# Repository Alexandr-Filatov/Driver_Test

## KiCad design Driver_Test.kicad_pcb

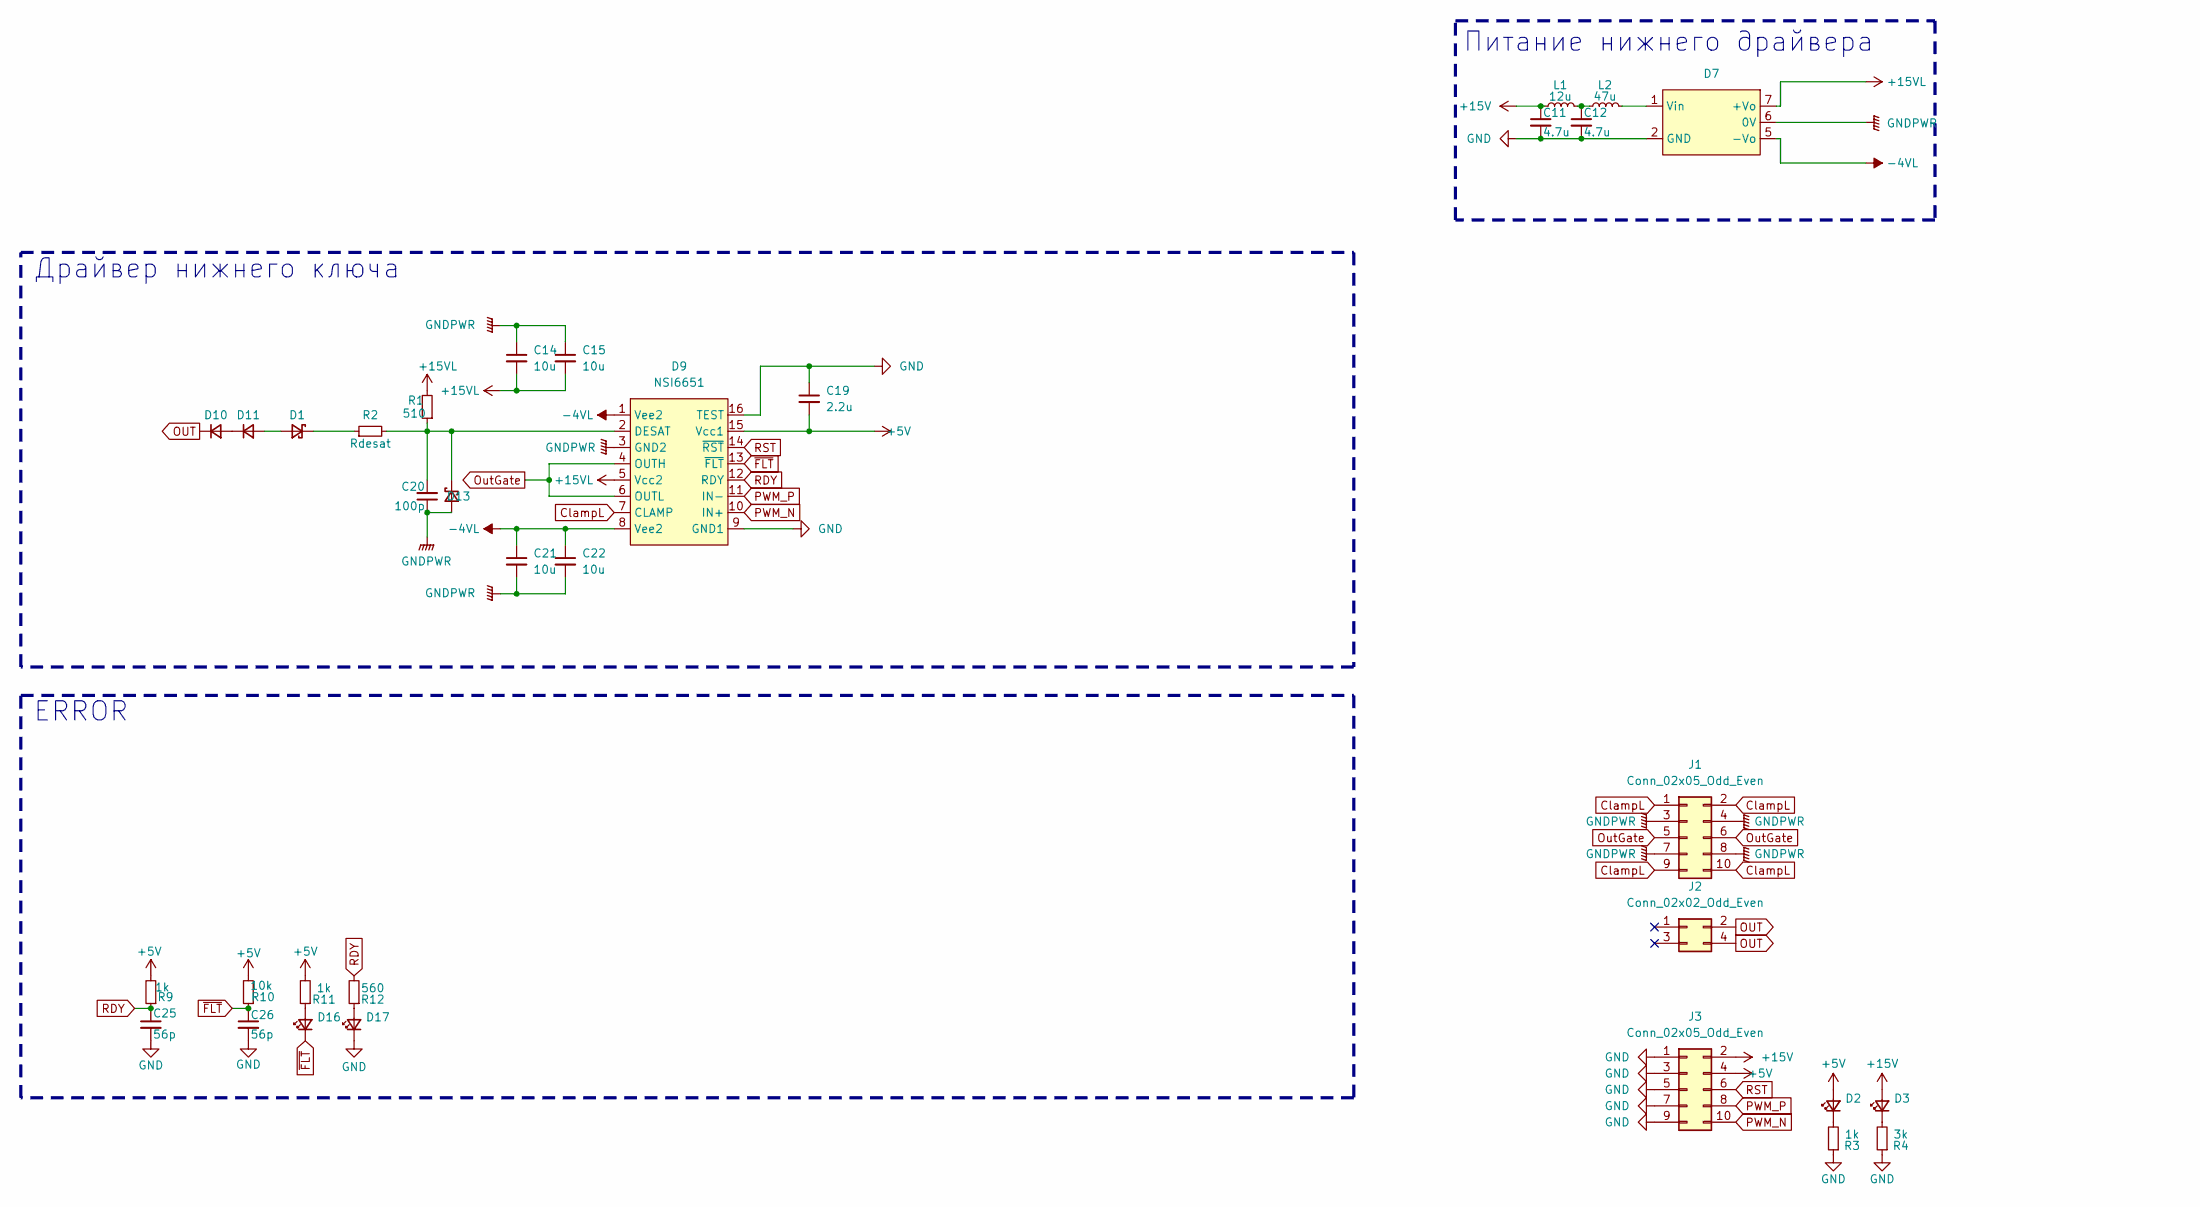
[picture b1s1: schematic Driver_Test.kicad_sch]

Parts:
C11, C12: 4.7u; C_1206_3216Metric_Pad1.33x1.80mm_HandSolder
C14, C15, C21, C22: 10u; C_1206_3216Metric_Pad1.33x1.80mm_HandSolder
C19: 2.2u; C_0805_2012Metric_Pad1.18x1.45mm_HandSolder
C20: 100p; C_0805_2012Metric_Pad1.18x1.45mm_HandSolder
C25, C26: 56p; C_0805_2012Metric_Pad1.18x1.45mm_HandSolder
D1: D_SOD-323_HandSoldering
D2, D3, D16, D17: LED_0805_2012Metric_Pad1.15x1.40mm_HandSolder
D7: QAxCx
D9: NSI6651; SOIC-16W_7.5x10.3mm_P1.27mm
D10, D11: D_Small; D_SMA_Handsoldering
D13: D_SOD-123
J1: Conn_02x05_Odd_Even; PinHeader_2x05_P2.54mm_Horizontal
J2: Conn_02x02_Odd_Even; PinHeader_2x02_P2.54mm_Horizontal
J3: Conn_02x05_Odd_Even; PinSocket_2x05_P2.54mm_Vertical
L1: 12u; L_1210_3225Metric_Pad1.42x2.65mm_HandSolder
L2: 47u; L_1812_4532Metric_Pad1.30x3.40mm_HandSolder
R1: 510; R_0805_2012Metric_Pad1.20x1.40mm_HandSolder
R2: Rdesat; R_0805_2012Metric_Pad1.20x1.40mm_HandSolder
R3, R9, R11: 1k; R_0805_2012Metric_Pad1.20x1.40mm_HandSolder
R4: 3k; R_0805_2012Metric_Pad1.20x1.40mm_HandSolder
R10: 10k; R_0805_2012Metric_Pad1.20x1.40mm_HandSolder
R12: 560; R_0805_2012Metric_Pad1.20x1.40mm_HandSolder

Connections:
+5V: C19.2, D2.2 (A), D9.15 (Vcc1), J3.4, R9.2, R10.2, R11.2
+15V: C11.1, D3.2 (A), J3.2, L1.1
+15VL: C14.2, C15.2, D7.7 (+Vo), D9.5 (Vcc2), R1.2
-15VL: C21.1, C22.1, D7.5 (-Vo), D9.1 (Vee2), D9.8 (Vee2)
ClampL: D9.7 (CLAMP), J1.1, J1.2, J1.9, J1.10
GND: C11.2, C12.2, C19.1, C25.2, C26.2, D7.2 (GND), D9.9 (GND1), D9.16 (TEST), D17.1 (K), J3.1, J3.3, J3.5, J3.7, J3.9, R3.1, R4.1
GNDPWR: C14.1, C15.1, C20.1, C21.2, C22.2, D7.6 (0V), D9.3 (GND2), D13.2 (A), J1.3, J1.4, J1.7, J1.8
unnamed: C12.1, L1.2, L2.1
unnamed: D1.2 (A), D11.2 (A)
unnamed: D1.1 (K), R2.1
unnamed: D2.1 (K), R3.2
unnamed: D3.1 (K), R4.2
unnamed: D7.1 (Vin), L2.2
unnamed: D10.2 (A), D11.1 (K)
unnamed: C20.2, D9.2 (DESAT), D13.1 (K), R1.1, R2.2
unnamed: D16.2 (A), R11.1
unnamed: D17.2 (A), R12.1
OUT: D10.1 (K), J2.2, J2.4
OutGate: D9.4 (OUTH), D9.6 (OUTL), J1.5, J1.6
PWM_N: D9.10 (IN+), J3.10
PWM_P: D9.11 (IN-), J3.8
RDY: C25.1, D9.12 (RDY), R9.1, R12.2
RST: D9.14 (~RST), J3.6
~FLT: C26.1, D9.13 (~FLT), D16.1 (K), R10.1

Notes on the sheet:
Драйвер нижнего ключа
Питание нижнего драйвера
ERROR

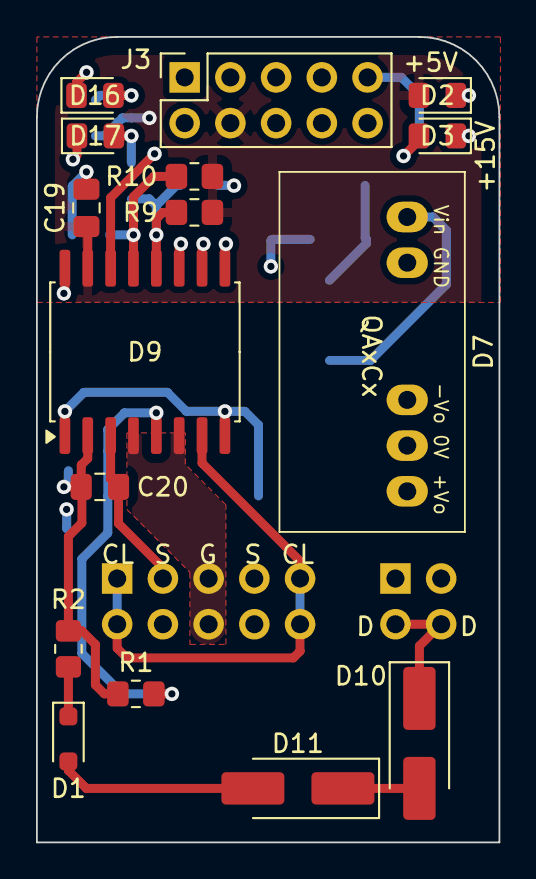
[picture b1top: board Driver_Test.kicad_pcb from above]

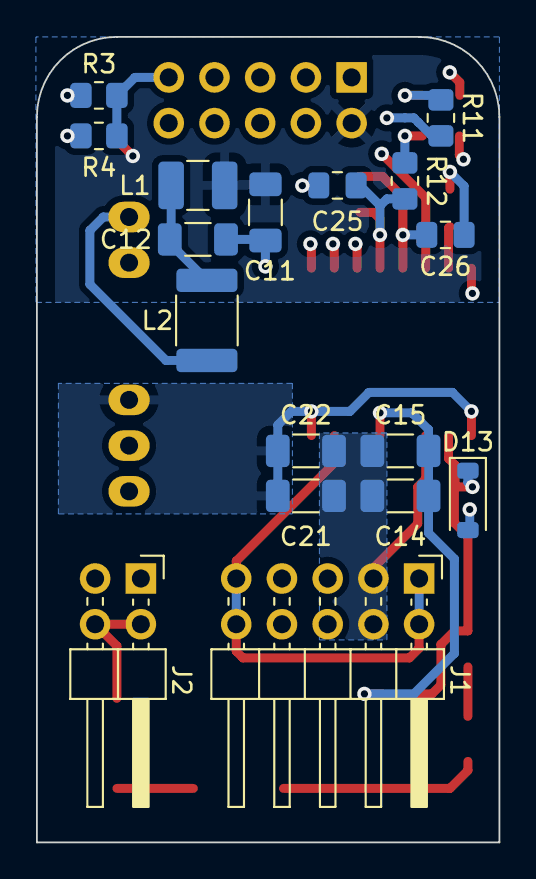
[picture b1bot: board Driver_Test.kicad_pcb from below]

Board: 4 copper layers, 25.7 x 44.8 mm, 33 parts (17 on the bottom side), 24 nets.

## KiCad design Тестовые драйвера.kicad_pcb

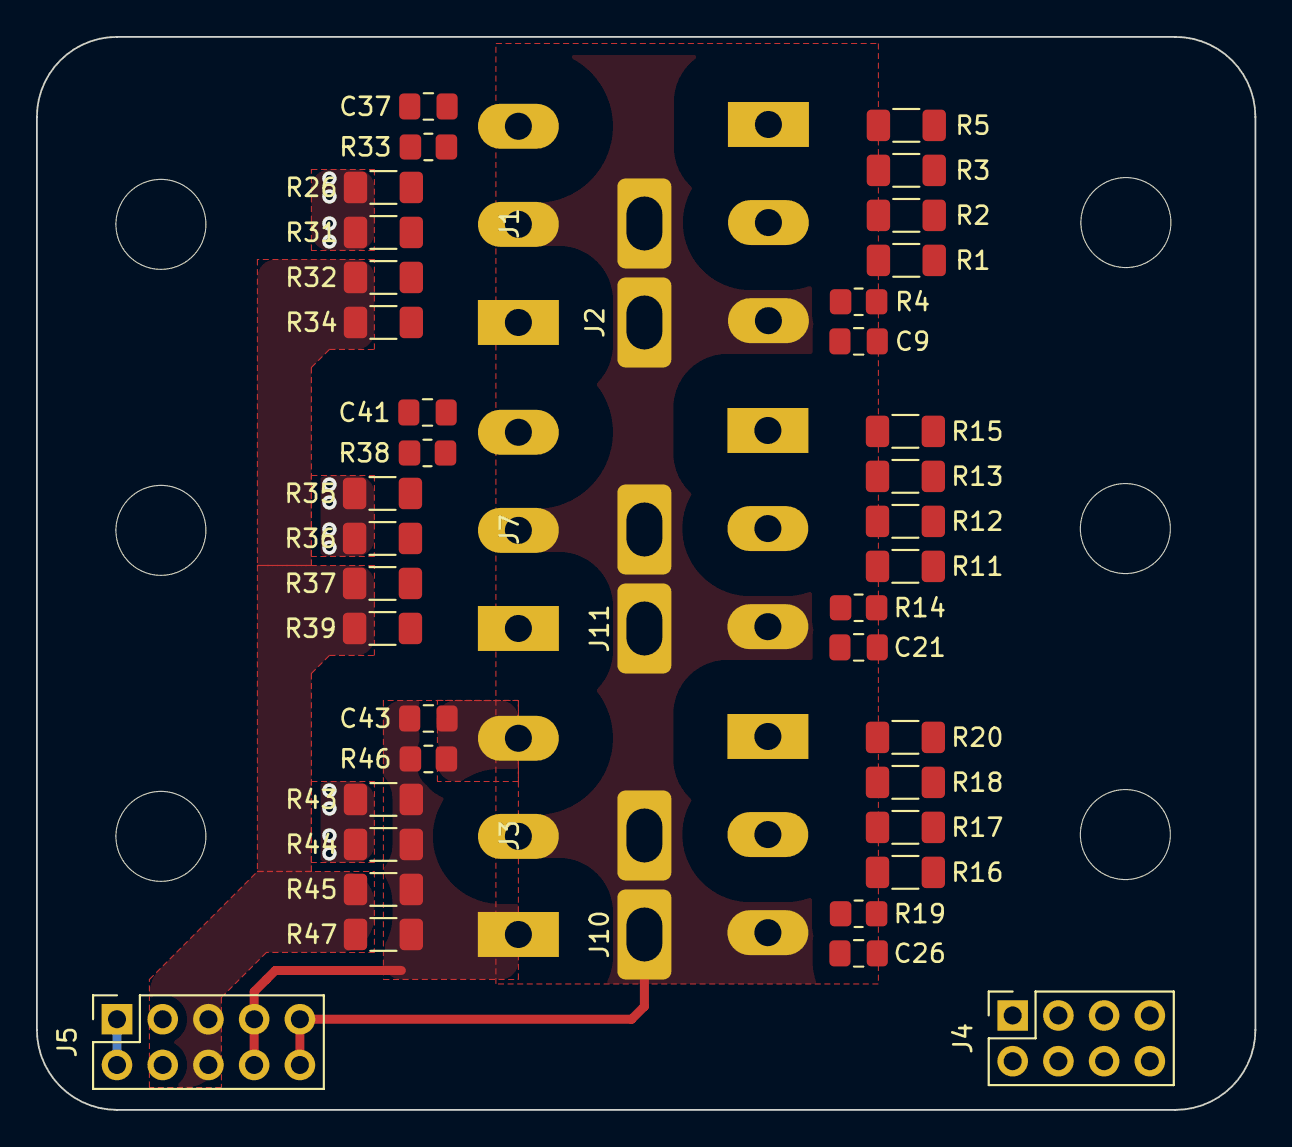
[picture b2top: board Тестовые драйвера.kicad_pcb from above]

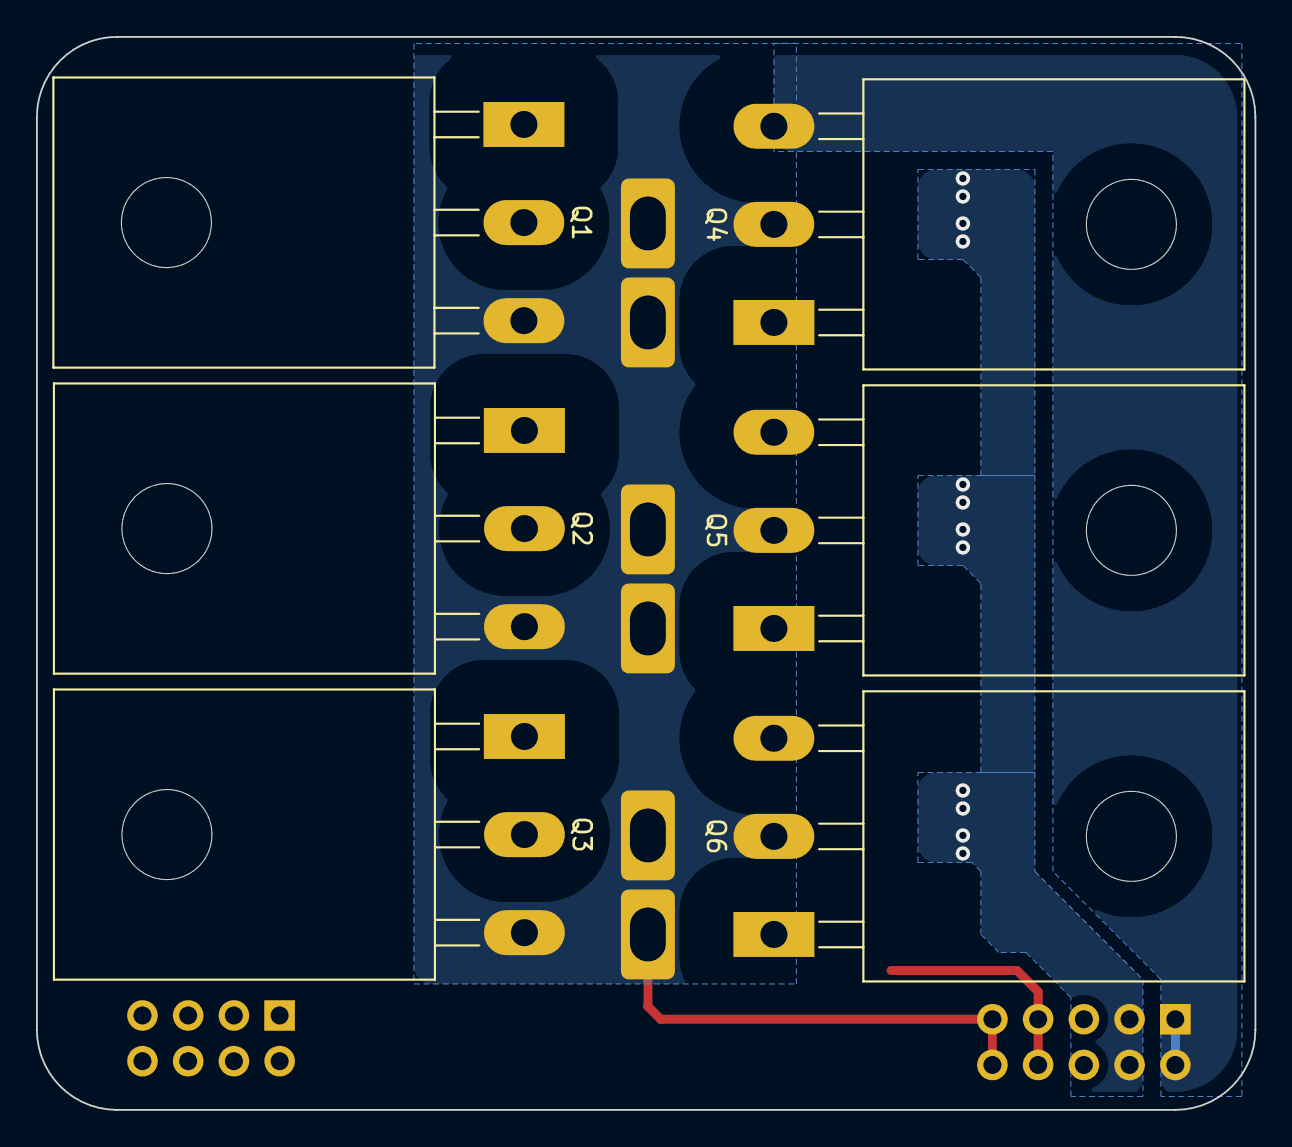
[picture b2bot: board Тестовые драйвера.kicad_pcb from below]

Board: 2 copper layers, 67.7 x 59.6 mm, 50 parts (6 on the bottom side), 9 nets.

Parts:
C9, C21, C26, C37, C41, C43: 10n; C_0805_2012Metric_Pad1.18x1.45mm_HandSolder
J1, J2, J3, J7, J10, J11: Conn_01x01; Bush_5x3
J4: Conn_01x04; PinSocket_2x04_P2.54mm_Vertical
J5: Conn_02x05_Odd_Even; PinSocket_2x05_P2.54mm_Vertical
Q1, Q2, Q3, Q4, Q5, Q6: C2M0280120D; TO-247-3_Horizontal_TabUp
R1, R2, R3, R5, R11, R12, R13, R15, R16, R17, R18, R20, R26, R31, R32, R34, R35, R36, R37, R39, R43, R44, R45, R47: 15; R_1206_3216Metric_Pad1.30x1.75mm_HandSolder
R4, R14, R19, R33, R38, R46: 10k; R_0805_2012Metric_Pad1.20x1.40mm_HandSolder

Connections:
ClampH: C9.1, C21.1, C26.1, Q1.1 (G), Q2.1 (G), Q3.1 (G), R1.2, R2.2, R3.1, R4.2, R5.1, R11.2, R12.2, R13.1, R14.2, R15.1, R16.2, R17.2, R18.1, R19.2, R20.1
ClampL: C37.1, C41.1, C43.1, J5.7, J5.8, Q4.1 (G), Q5.1 (G), Q6.1 (G), R26.2, R31.2, R32.1, R33.2, R34.1, R35.2, R36.2, R37.1, R38.2, R39.1, R43.2, R44.2, R45.1, R46.2, R47.1
GNDPWR: C37.2, C41.2, C43.2, J5.1, J5.2, Q4.3 (S), Q5.3 (S), Q6.3 (S), R33.1, R38.1, R46.1
OUT: C9.2, C21.2, C26.2, J1.1, J2.1, J3.1, J5.9, J5.10, J7.1, J10.1, J11.1, Q1.3 (S), Q2.3 (S), Q3.3 (S), Q4.2 (D), Q5.2 (D), Q6.2 (D), R4.1, R14.1, R19.1
OutH1: R1.1, R2.1, R11.1, R12.1, R16.1, R17.1
OutH2: J5.3, J5.4, R26.1, R31.1, R35.1, R36.1, R43.1, R44.1
OutL1: R3.2, R5.2, R13.2, R15.2, R18.2, R20.2
OutL2: J5.5, J5.6, R32.2, R34.2, R37.2, R39.2, R45.2, R47.2
VDC: Q1.2 (D), Q2.2 (D), Q3.2 (D)

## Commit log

2024-05-22 Нулевой коммит
2024-05-23 Полная схема
2024-05-23 Начал разводку платы
2024-06-08 Расположил на плате
2024-06-09 Разве драйвера
2024-06-19 Закончил схему и разводку платы
2025-08-28 Пытаюсь сделать как у вольфспида
2025-09-10 VER1.0: пробую уложиться в ширину транзисторов
2025-10-13 Пытаюсь уложиться в контур транзисторов
2025-10-14 Определились с ТЗ
2025-11-25 VER1.0: разделил плату драйвера и силовую
2025-11-28 VER1.0: поработал над шинами
2025-12-01 VER1.0.1: убрал вводы шин наружу от ножек транзисторов
2025-12-02 VER1.0.2: развел нижнюю сторону
2025-12-04 VER1.0.2: убрал из проекта силу
2025-12-10 VER1.0.2: сделал плату на один ключ
2025-12-15 VER1.0.2: обновил модель платы драйверов
2026-01-22 VER1.0.2: развел все дорожки, добавил светодиоды по питанию
